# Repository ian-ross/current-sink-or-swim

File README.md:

# Active current sink driven by Teensy 4.0

This started as the *Current Sink Or Swim* project from [Contextual
Electronics](https://contextualelectronics.com/), but I decided to
make it programmable by adding a Teensy.

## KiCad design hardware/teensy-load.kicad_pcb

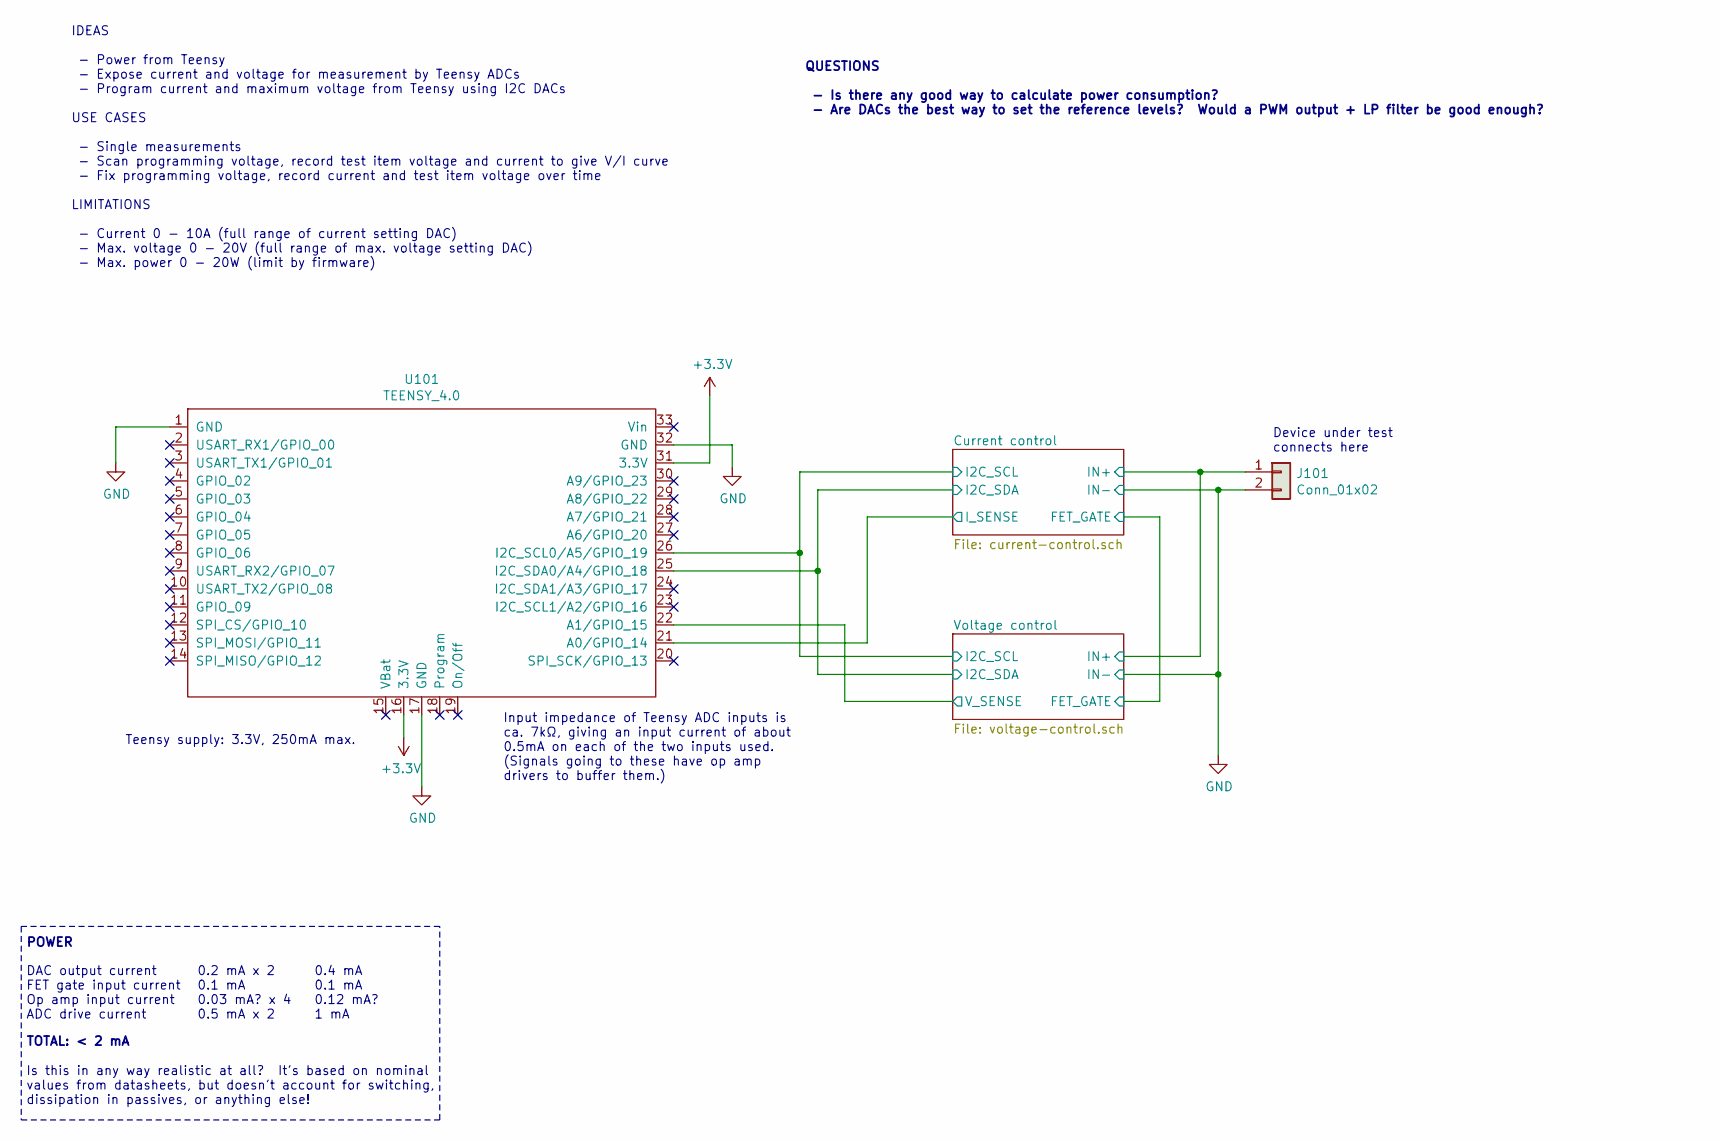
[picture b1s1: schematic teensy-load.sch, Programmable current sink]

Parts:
J101: Conn_01x02; TerminalBlock_Phoenix_MKDS-3-2-5.08_1x02_P5.08mm_Horizontal; MPN TB010-508-02BE
U101: TEENSY_4.0; MPN TEENSY 4.0

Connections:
+3V3: U101.16 (3.3V), U101.31 (3.3V); also elsewhere on the board
/Current control/I2C_SCL: U101.26 (I2C_SCL0/A5/GPIO_19); also elsewhere on the board
/Current control/I2C_SDA: U101.25 (I2C_SDA0/A4/GPIO_18); also elsewhere on the board
/Current control/IN+: J101.1; also elsewhere on the board
/Current control/I_SENSE: U101.21 (A0/GPIO_14); also elsewhere on the board
/Voltage control/V_SENSE: U101.22 (A1/GPIO_15); also elsewhere on the board
GND: J101.2, U101.1 (GND), U101.17 (GND), U101.32 (GND); also elsewhere on the board

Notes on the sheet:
IDEAS - Power from Teensy - Expose current and voltage for measurement by Teensy ADCs - Program current and maximum voltage from Teensy using I2C DACs USE CASES - Single measurements - Scan programming voltage, record test item voltage and current to give V/I curve - Fix programming voltage, record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
Teensy supply: 3.3V, 250mA max.
Device under test connects here
Input impedance of Teensy ADC inputs is ca. 7kΩ, giving an input current of about 0.5mA on each of the two inputs used. (Signals going to these have op amp drivers to buffer them.)
POWER
DAC output current FET gate input current Op amp input current ADC drive current
TOTAL: < 2 mA
0.2 mA x 2 0.1 mA 0.03 mA? x 4 0.5 mA x 2
0.4 mA 0.1 mA 0.12 mA? 1 mA
Is this in any way realistic at all? It's based on nominal values from datasheets, but doesn't account for switching, dissipation in passives, or anything else!
QUESTIONS - Is there any good way to calculate power consumption? - Are DACs the best way to set the reference levels? Would a PWM output + LP filter be good enough?

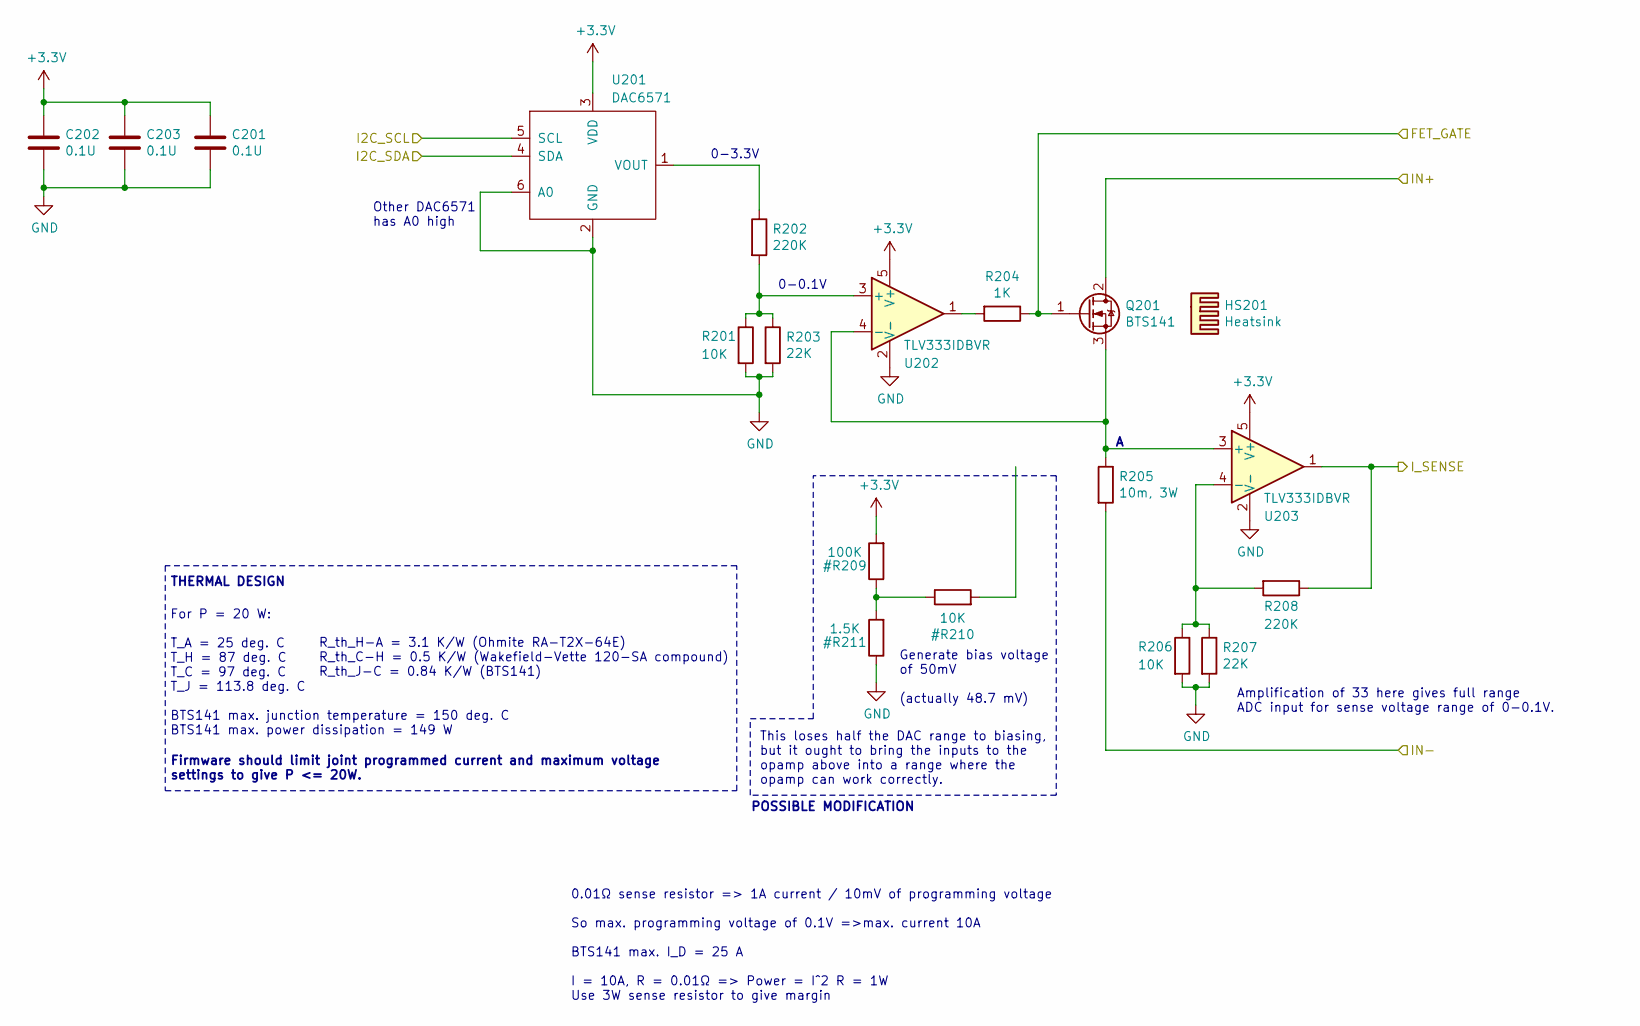
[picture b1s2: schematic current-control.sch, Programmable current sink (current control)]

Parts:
C201, C202, C203: 0.1U; C_0805_2012Metric_Pad1.15x1.40mm_HandSolder; MPN 885012207098
HS201: Heatsink; HeatSink_RA_T2X_64E; MPN RA-T2X-64E
Q201: BTS141; TO-220-3_Vertical; MPN BTS141BKSA1
R201, R206: 10K; R_0805_2012Metric_Pad1.15x1.40mm_HandSolder; MPN CRGP0805F1K0
R202, R208: 220K; R_0805_2012Metric_Pad1.15x1.40mm_HandSolder; MPN CRGP0805F220K
R203, R207: 22K; R_0805_2012Metric_Pad1.15x1.40mm_HandSolder; MPN CRGP0805F22K
R204: 1K; R_0805_2012Metric_Pad1.15x1.40mm_HandSolder; MPN CRGP0805F1K0
R205: 10m, 3W; Sense_Resistor; MPN RMCJ2U00R01FS
U201: DAC6571; SOT-23-6_Handsoldering; MPN DAC6571IDBVR
U202, U203: TLV333IDBVR; SOT-23-5

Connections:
+3V3: C201.1, C202.1, C203.1, U201.3 (VDD), U202.5 (V+), U203.5 (V+); also elsewhere on the board
/Current control/FET_GATE: Q201.1 (G), R204.1; also elsewhere on the board
/Current control/I2C_SCL: U201.5 (SCL); also elsewhere on the board
/Current control/I2C_SDA: U201.4 (SDA); also elsewhere on the board
/Current control/IN+: Q201.2 (D); also elsewhere on the board
/Current control/I_SENSE: R208.1, U203.1; also elsewhere on the board
GND: C201.2, C202.2, C203.2, R201.2, R203.2, R205.2, R206.2, R207.2, U201.2 (GND), U201.6 (A0), U202.2 (V-), U203.2 (V-); also elsewhere on the board
unnamed: Q201.3 (S), R205.1, U202.4 (-), U203.3 (+)
unnamed: R201.1, R202.2, R203.1, U202.3 (+)
unnamed: R202.1, U201.1 (VOUT)
unnamed: R204.2, U202.1
unnamed: R206.1, R207.1, R208.2, U203.4 (-)

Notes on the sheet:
0.01Ω sense resistor => 1A current / 10mV of programming voltage So max. programming voltage of 0.1V =>max. current 10A BTS141 max. I_D = 25 A I = 10A, R = 0.01Ω => Power = I^2 R = 1W Use 3W sense resistor to give margin
0-3.3V
0-0.1V
Other DAC6571 has A0 high
THERMAL DESIGN
For P = 20 W: T_A = 25 deg. C T_H = 87 deg. C T_C = 97 deg. C T_J = 113.8 deg. C BTS141 max. junction temperature = 150 deg. C BTS141 max. power dissipation = 149 W
R_th_H-A = 3.1 K/W (Ohmite RA-T2X-64E) R_th_C-H = 0.5 K/W (Wakefield-Vette 120-SA compound) R_th_J-C = 0.84 K/W (BTS141)
Firmware should limit joint programmed current and maximum voltage settings to give P <= 20W.
Amplification of 33 here gives full range ADC input for sense voltage range of 0-0.1V.
Generate bias voltage of 50mV (actually 48.7 mV)
This loses half the DAC range to biasing, but it ought to bring the inputs to the opamp above into a range where the opamp can work correctly.
POSSIBLE MODIFICATION

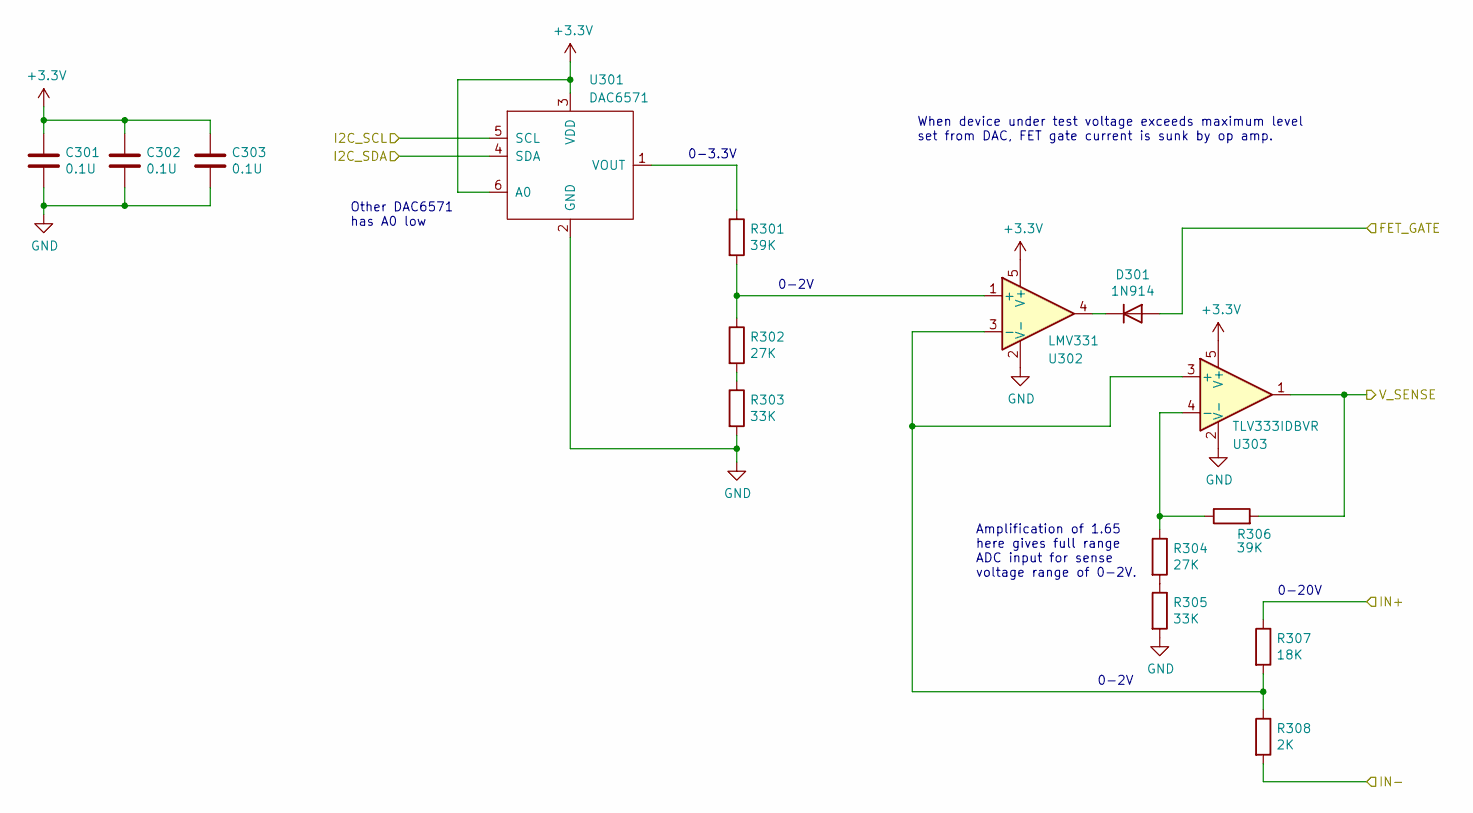
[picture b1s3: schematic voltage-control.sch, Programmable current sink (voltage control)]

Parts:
C301, C302, C303: 0.1U; C_0805_2012Metric_Pad1.15x1.40mm_HandSolder; MPN 885012207098
D301: 1N914; D_SOD-123F; MPN 1N914BW RH
R301, R306: 39K; R_0805_2012Metric_Pad1.15x1.40mm_HandSolder; MPN CRCW040239K0FKEDC
R302, R304: 27K; R_0805_2012Metric_Pad1.15x1.40mm_HandSolder; MPN CRCW120627K0FKEAC
R303, R305: 33K; R_0805_2012Metric_Pad1.15x1.40mm_HandSolder; MPN CRGP0805F33K
R307: 18K; R_0805_2012Metric_Pad1.15x1.40mm_HandSolder; MPN CRGP0805F18K
R308: 2K; R_0805_2012Metric_Pad1.15x1.40mm_HandSolder; MPN CRCW08052K00FKEAC
U301: DAC6571; SOT-23-6_Handsoldering; MPN DAC6571IDBVR
U302: LMV331; SOT-23-5
U303: TLV333IDBVR; SOT-23-5

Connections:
+3V3: C301.1, C302.1, C303.1, U301.3 (VDD), U301.6 (A0), U302.5 (V+), U303.5 (V+); also elsewhere on the board
/Current control/FET_GATE: D301.2 (A); also elsewhere on the board
/Current control/I2C_SCL: U301.5 (SCL); also elsewhere on the board
/Current control/I2C_SDA: U301.4 (SDA); also elsewhere on the board
/Current control/IN+: R307.1; also elsewhere on the board
/Voltage control/V_SENSE: R306.2, U303.1; also elsewhere on the board
GND: C301.2, C302.2, C303.2, R303.2, R305.2, R308.2, U301.2 (GND), U302.2 (V-), U303.2 (V-); also elsewhere on the board
unnamed: D301.1 (K), U302.4
unnamed: R301.1, U301.1 (VOUT)
unnamed: R301.2, R302.1, U302.1 (+)
unnamed: R302.2, R303.1
unnamed: R304.1, R306.1, U303.4 (-)
unnamed: R304.2, R305.1
unnamed: R307.2, R308.1, U302.3 (-), U303.3 (+)

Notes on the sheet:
0-3.3V
0-2V
Other DAC6571 has A0 low
0-20V
When device under test voltage exceeds maximum level set from DAC, FET gate current is sunk by op amp.
Amplification of 1.65 here gives full range ADC input for sense voltage range of 0-2V.

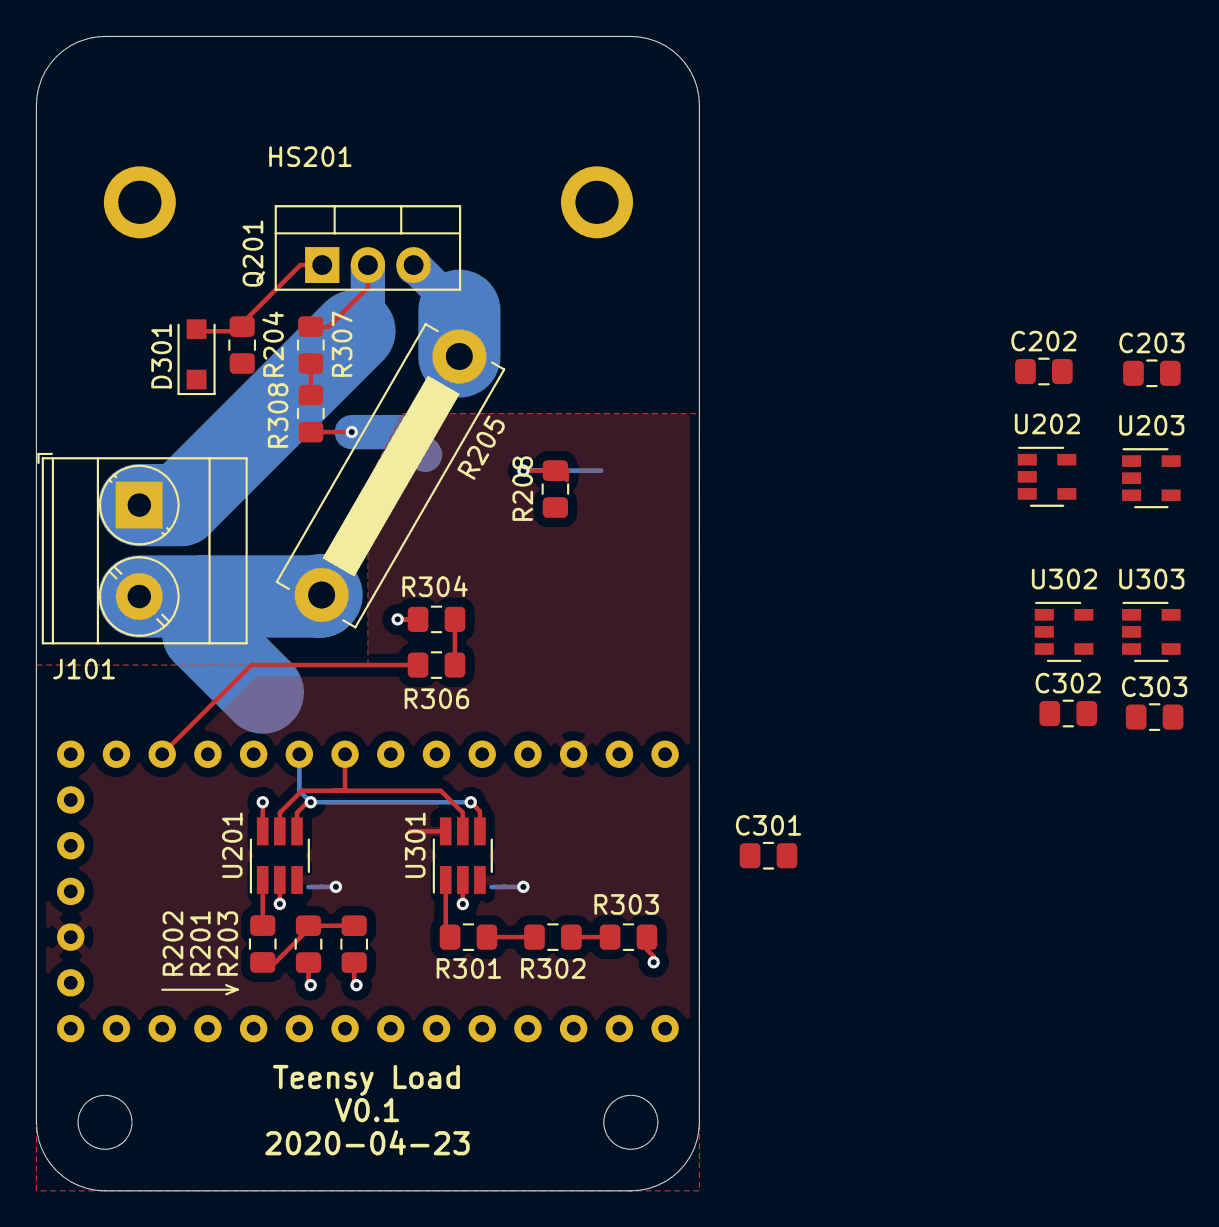
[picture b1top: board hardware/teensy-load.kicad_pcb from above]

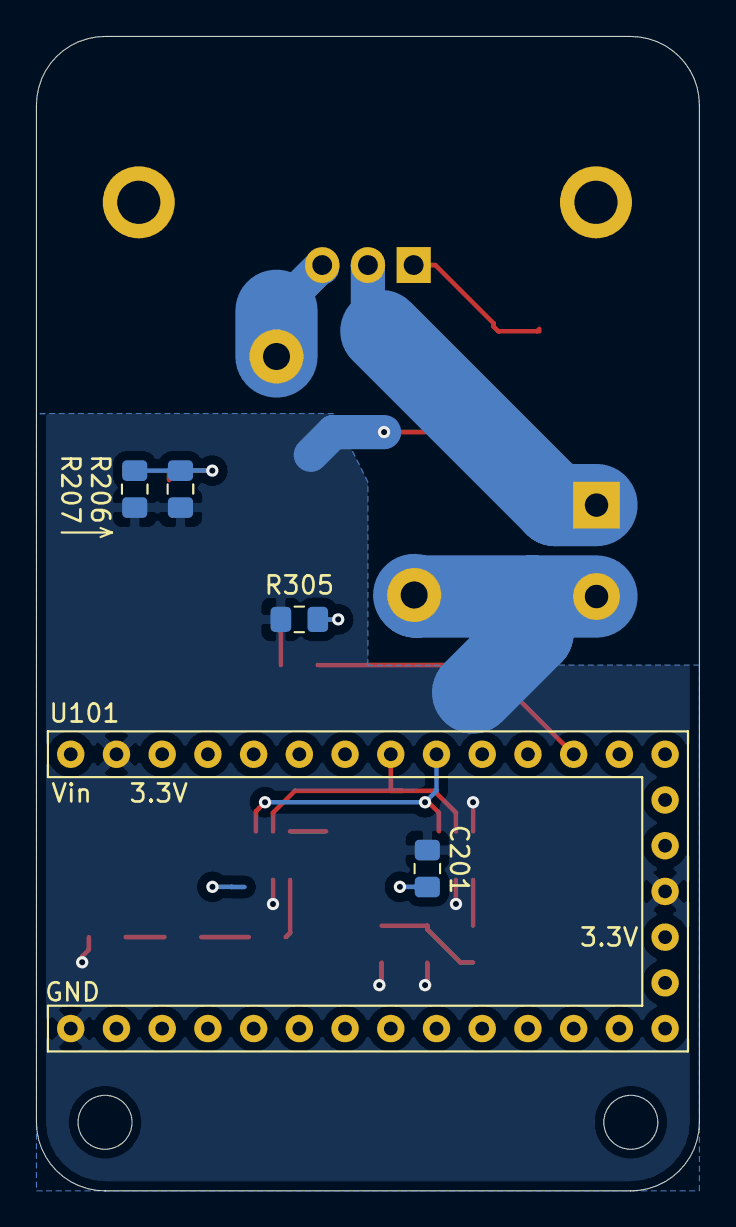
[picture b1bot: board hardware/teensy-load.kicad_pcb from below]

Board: 2 copper layers, 36.8 x 64.1 mm, 33 parts (5 on the bottom side), 20 nets.

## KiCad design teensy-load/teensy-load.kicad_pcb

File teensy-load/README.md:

# Contextual Electronics active current sink project

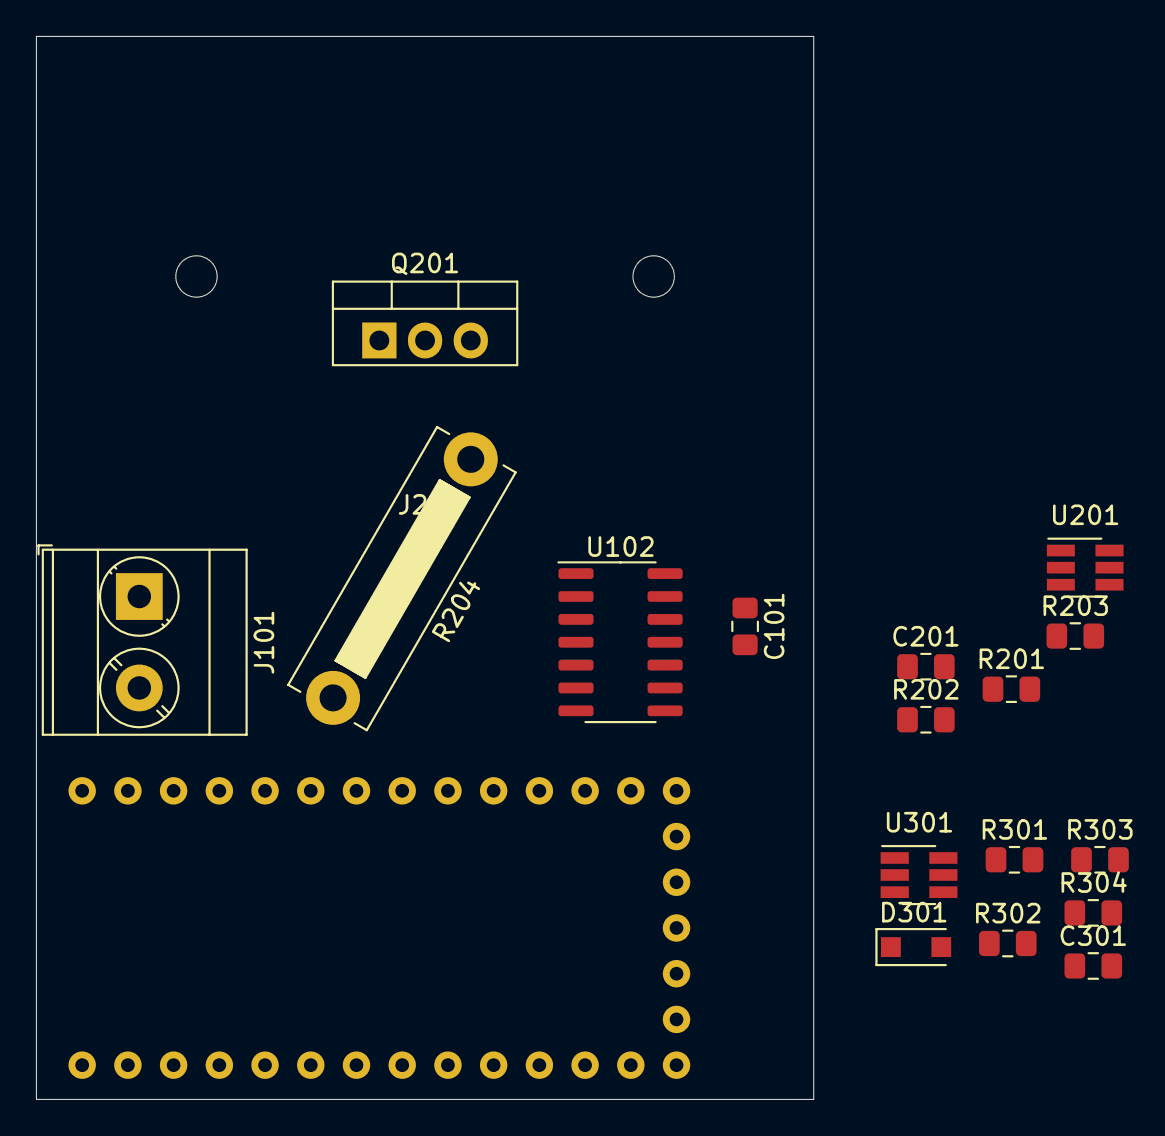
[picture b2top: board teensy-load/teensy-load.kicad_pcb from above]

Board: 2 copper layers, 43.2 x 59.1 mm, 19 parts (1 on the bottom side), 16 nets, no tracks yet.

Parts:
C101, C201, C301: 0.1U; C_0805_2012Metric_Pad1.15x1.40mm_HandSolder
D301: 1N914; D_SOD-123F
J101: Conn_01x02; TerminalBlock_Phoenix_MKDS-3-2-5.08_1x02_P5.08mm_Horizontal
J201: Conn_01x01_Male; HeatSink_RA_T2X_64E
Q201: BTS141; TO-220-3_Vertical
R201: 23K; R_0805_2012Metric_Pad1.15x1.40mm_HandSolder
R202, R301: 10K; R_0805_2012Metric_Pad1.15x1.40mm_HandSolder
R203, R304: 1K; R_0805_2012Metric_Pad1.15x1.40mm_HandSolder
R204: 0.1, 1W; Sense_Resistor
R302: 15K; R_0805_2012Metric_Pad1.15x1.40mm_HandSolder
R303: 9K; R_0805_2012Metric_Pad1.15x1.40mm_HandSolder
U101: TEENSY_4.0
U102: TLV4333; SOIC-14_3.9x8.7mm_P1.27mm
U201, U301: DAC6571; SOT-23-6_Handsoldering

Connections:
+3V3: C101.1, C201.1, C301.1, U101.16, U101.31, U102.4, U201.3, U301.3, U301.6
/Current control/FET_GATE: D301.1, Q201.1, R203.1
/Current control/I2C_SCL: U101.26, U201.5, U301.5
/Current control/I2C_SDA: U101.25, U201.4, U301.4
/Current control/IN+: J101.1, Q201.2, R303.1
/Current control/I_SENSE: U101.21, U102.6, U102.7
/Voltage control/V_SENSE: U101.22, U102.13, U102.14
GND: C101.2, C201.2, C301.2, J101.2, R202.2, R204.2, R302.2, R304.2, U101.1, U101.17, U101.32, U102.11, U201.2, U201.6, U301.2
unnamed: D301.2, U102.8
unnamed: Q201.3, R204.1, U102.2, U102.5
unnamed: R201.1, U201.1
unnamed: R201.2, R202.1, U102.3
unnamed: R203.2, U102.1
unnamed: R301.1, U301.1
unnamed: R301.2, R302.1, U102.10
unnamed: R303.2, R304.1, U102.9, U102.12

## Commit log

2020-03-15 Moving things around a little
2020-03-15 Ignore
2020-04-18 After footprint check, before layout
2020-04-22 Initial component placement
2020-04-22 Layout done
2020-04-23 Check-in before redoing layout
2020-04-23 V0.1 layout for manufacture
2020-04-23 Add V0.1 BOM
2020-04-26 First draft of firmware.
2020-04-29 UI for meter mode application
2020-04-30 Start on firmware in PlatformIO
2020-05-07 Organise firmware; add simulator
2020-07-16 Tidying
2020-07-18 First working (?) version of tl-meter
2020-07-18 Add possible biasing modification to schematic
2020-07-18 Data saving
2020-07-18 Comments in tl-meter data files
2020-07-19 TL meter UI improvements
2020-07-19 Disable TL on tl-meter close
2020-07-20 Freeze PIP dependencies
2020-07-24 Fix #1
2020-07-24 Fix #2
2020-08-15 Calibration, tl-discharge (untested)
2020-08-15 Start of revision 2 design changes
